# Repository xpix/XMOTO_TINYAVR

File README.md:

# Documentation for Motor Controller with PID Control to use a DC motor as stepper/servo

This code is designed for a motor controller and has merged the PID code of Josh Kopel with the code of the Makerbot servo-controller board. This code can be used on some boards by changing some values.

## Hardware Requirements

- motor controller as H-Bridge
- Hall Sensor PCB
- Ramps 1.4 stepper driver

## Software Requirements

- PID_v2.h library
- EEPROM.h library

## Code Explanation

### Motor Driver Type

The type of motor driver is defined using the `PWMCONTROL` variable. If `PWMCONTROL` is set to `1`, it means that the motor driver has only a PWM interface. In this case, the minimum and maximum values for PWM to turn the motor are defined using `PWMMIN` and `PWMMAX`.

### Pin Definitions

The pins used in the code are defined as follows:

- `encoder0PinA` and `encoder0PinB`: Pins for the Hall Sensor PCB
- `MotorIN1` and `MotorIN2`: Pins for the motor driver (if `PWMCONTROL` is set to `1`)
- `MotorDIR` and `MotorPWM`: Pins for the motor driver (if `PWMCONTROL` is set to `0`)
- `STEP_PIN` and `DIR_PIN`: Pins for the Ramps 1.4 stepper driver
- `EnableLED`: Pin for the LED that signals if the MCU is running

### PID Values

The default PID values are defined using the `MyObject` struct. The `kp`, `ki`, and `kd` values are set to `7.00`, `0.04`, and `0.20` respectively. These values can be changed by the user.

### Setup Function

In the `setup()` function, the following tasks are performed:

- Serial communication is started at a baud rate of 9600.
- The saved PID values are retrieved from the EEPROM. If no values are saved, the default values are used.
- The pins are set to their respective modes.
- Interrupts are attached to the `encoder0PinA` and `STEP_PIN` pins.
- The PID is set to automatic mode with a sample time of 2 and an output limit of -255 to 255.

### Loop Function

In the `loop()` function, the following tasks are performed:

- The set

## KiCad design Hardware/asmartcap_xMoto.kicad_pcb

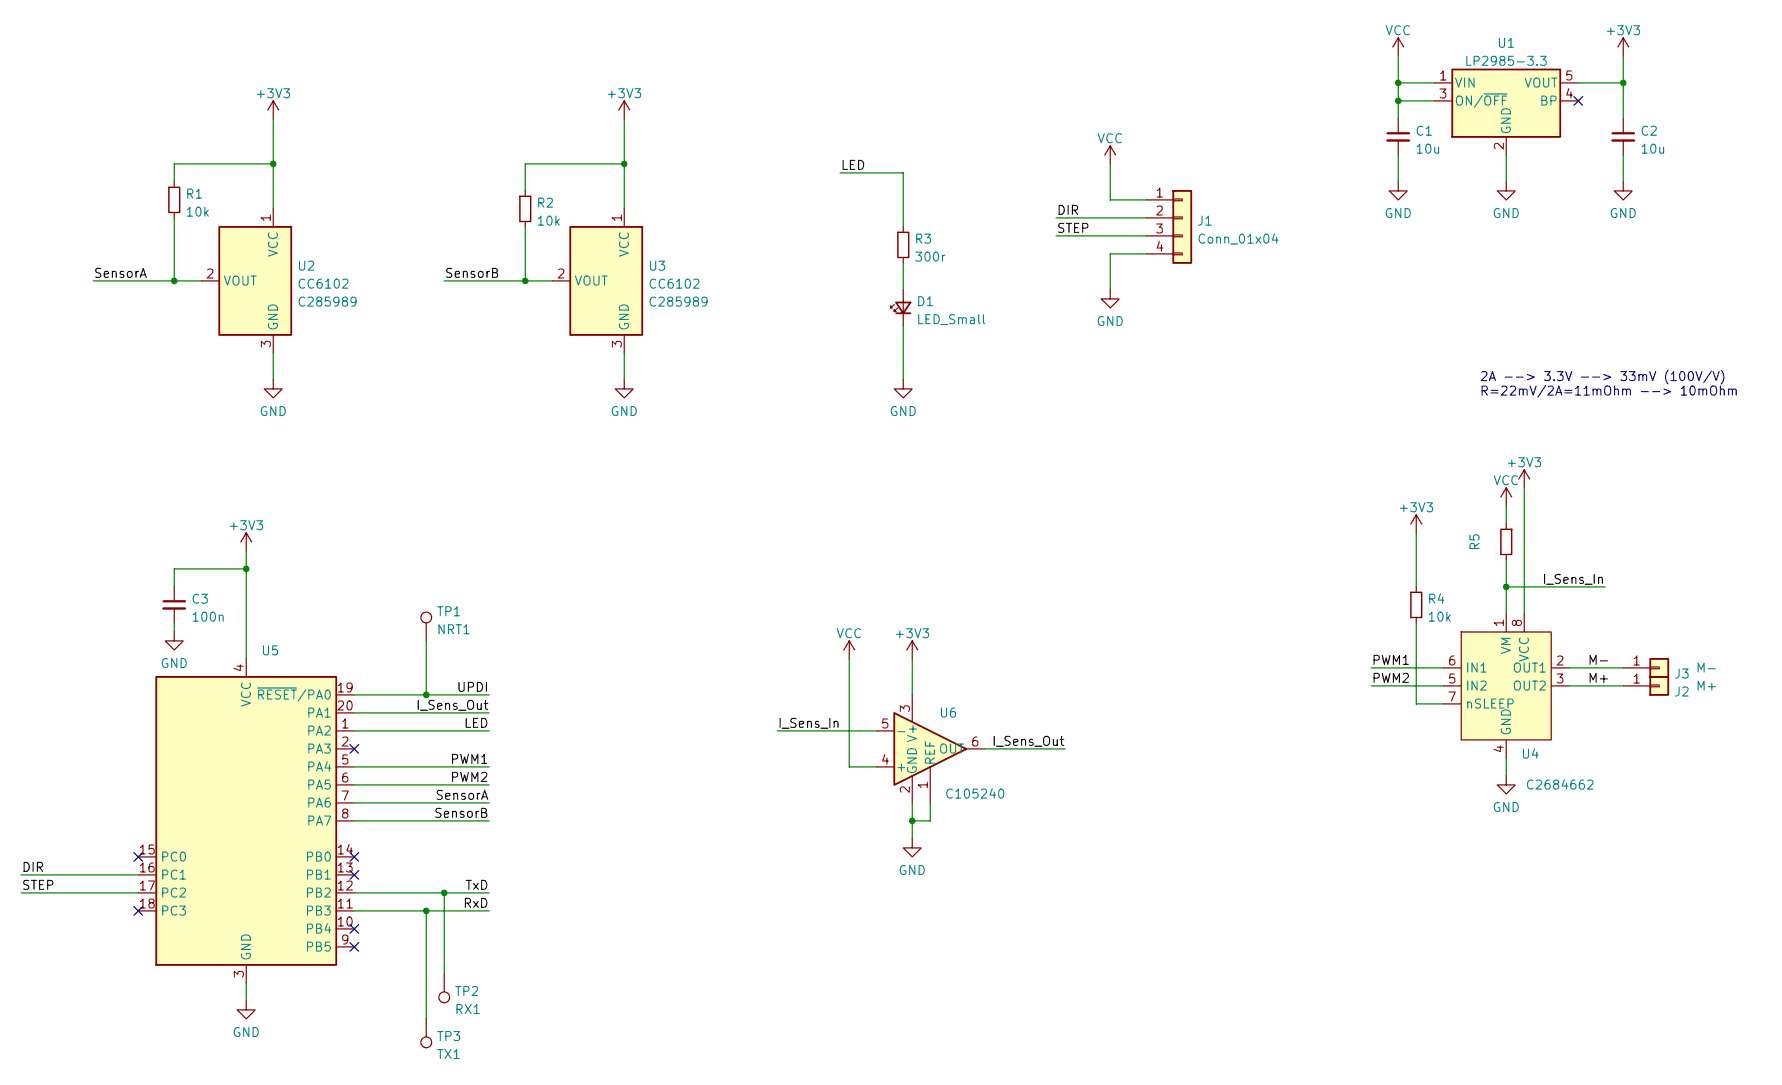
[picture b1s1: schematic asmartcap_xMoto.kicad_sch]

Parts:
C1, C2: 10u; C_0402_1005Metric; LCSC C15525
C3: 100n; C_0402_1005Metric
D1: LED_Small; LED_0402_1005Metric
J1: Conn_01x04; PinHeader_1x04_P2.54mm_Horizontal
J2: M+; TestPoint_Plated_Hole_D3.0mm
J3: M-; TestPoint_Plated_Hole_D3.0mm
R1, R2, R4: 10k; R_0402_1005Metric; MPN 0402WGF3000TCE; LCSC C25102
R3: 300r; R_0402_1005Metric
R5: MPN RTT03R010FTP; JLCPCB C158899
TP1: NRT1; TestPoint_Pad_D1.5mm
TP2: RX1; TestPoint_Pad_D1.5mm
TP3: TX1; TestPoint_Pad_D1.5mm
U1: LP2985-3.3; SOT-23-5
U2, U3: CC6102; TSOT-23; LCSC C285989
U4: LCSC C2684662
U5: (no value)
U6: JLCPCB C105240

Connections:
+3V3: C2.1, C3.1, R1.1, R2.1, R4.1, U1.5 (VOUT), U2.1 (VCC), U3.1 (VCC), U4.8 (VCC), U5.4 (VCC), U6.3 (V+)
/DIR: J1.2, U5.16 (PC1)
/I_Sens_In: R5.2, U4.1 (VM), U6.5 (-)
/I_Sens_Out: U5.20 (PA1), U6.6 (OUT)
/LED: R3.1, U5.1 (PA2)
/M+: J2.1, U4.3 (OUT2)
/M-: J3.1, U4.2 (OUT1)
/PWM1: U4.6 (IN1), U5.5 (PA4)
/PWM2: U4.5 (IN2), U5.6 (PA5)
/RxD: TP3.1, U5.11 (PB3)
/STEP: J1.3, U5.17 (PC2)
/SensorA: R1.2, U2.2 (VOUT), U5.7 (PA6)
/SensorB: R2.2, U3.2 (VOUT), U5.8 (PA7)
/TxD: TP2.1, U5.12 (PB2)
/UPDI: TP1.1, U5.19 (~RESET/PA0)
GND: C1.2, C2.2, C3.2, D1.1 (K), J1.4, U1.2 (GND), U2.3 (GND), U3.3 (GND), U4.4 (GND), U4.9 (Pad), U5.3 (GND), U5.21 (GND), U6.1 (REF), U6.2 (GND)
unnamed: D1.2 (A), R3.2
unnamed: R4.2, U4.7 (nSLEEP)
VCC: C1.1, J1.1, R5.1, U1.1 (VIN), U1.3 (ON/~OFF), U6.4 (+)

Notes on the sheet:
2A --> 3.3V --> 33mV (100V/V) R=22mV/2A=11mOhm --> 10mOhm

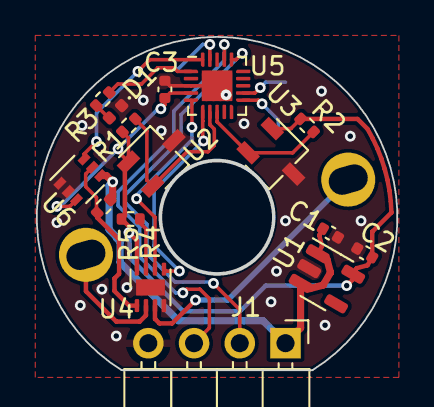
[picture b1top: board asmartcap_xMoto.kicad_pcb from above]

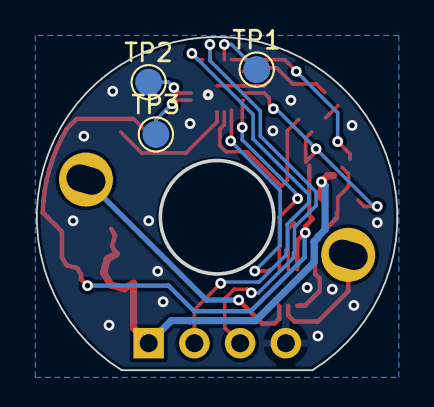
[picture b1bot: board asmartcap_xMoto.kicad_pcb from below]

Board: 2 copper layers, 19.9 x 18.4 mm, 21 parts (3 on the bottom side), 19 nets.

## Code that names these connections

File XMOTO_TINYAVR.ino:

/* 

i have made this code for the LMD18245 motor controller, 
i have merged the pid code of  Josh Kopel 
whith the code of makerbot servo-controller board,
you can use this code on the some board changing some values.
Daniele Poddighe

https://github.com/sebleedelisle/freeservo/tree/master/ServoStrap-master

Changes from Frank Herrmann for XMOTO and XMOTOD20

*/ 

#include <PID_v2.h>
#include <EEPROM.h>

#if defined(MILLIS_USE_TIMERA0)||defined(__AVR_ATtinyxy2__)
  #error "This sketch takes over TCA0, don't use for millis here.  Pin mappings on 8-pin parts are different"
#endif

// Type of Motordriver as is, with just an PWM Interface = true
// DRV8803
#define PWMCONTROL        1
#define PWMMIN           90 // minimum value for PWM to turn the motor
#define PWMMAX          200 // maximum value for PWM

#define EEPIDADDR         1 // Adress for saved PID Values

// Connect to Hall Sensor PCB
#define encoder0PinA  	2 // PA6
#define encoder0PinB  	3 // PA7

// If u need an revert, please change here the pins to motorcontroller
#if PWMCONTROL
  #define MotorIN1        1 // PA4
  #define MotorIN2        0 // PA5
#else
  #define MotorDIR    	  0 // PA4
  #define MotorPWM 		    1 // PA5
#endif

//from ramps 1.4 stepper driver
#define STEP_PIN	      12 // PC2
#define DIR_PIN         11 // PC1
#define EnableLED       15 // PB6


volatile long encoder0Pos = 0;

long GetSteps = 0;

// PID default values 
struct MyObject {
  double kp;
  double ki;
  double kd;
};
MyObject PIDvals = {
  1.35, 0.00, 0.01 // defaut values for PID
};

double input = 0, output = 0, setpoint = 0, error = 0;
PID myPID(&input, &output, &setpoint, PIDvals.kp, PIDvals.ki, PIDvals.kd, DIRECT);  

long LastInterval = 0;
long previousMillis = 0;        // will store last time LED was updated
bool dir     = false;

// ---------------------- SETUP -----------------------
void setup() { 
	Serial.begin(9600);

  pinMode(EnableLED, OUTPUT);
  digitalWrite (EnableLED, HIGH);

  // get Saved (EEPROM) or default PID Values
  MyObject PIDv;
  EEPROM.get(EEPIDADDR, PIDv);
  if(not (PIDv.kp > 0.01)){
     PIDv = {
        PIDvals.kp, PIDvals.ki, PIDvals.kd // defaut values
     };
  }
  myPID.SetTunings(PIDv.kp, PIDv.ki, PIDv.kd);
  Serial.println("Saved (EEPROM) or default PID Values:");
  Serial.println(PIDv.kp);
  Serial.println(PIDv.ki);
  Serial.println(PIDv.kd);

  myPID.SetMode(AUTOMATIC);     //set PID in Auto mode
  myPID.SetSampleTime(2);     // refresh rate of PID controller
  myPID.SetOutputLimits(-255, 255); // this is the MAX PWM value to move motor

	// Set Pins 
	pinMode(encoder0PinA, INPUT); 
	pinMode(encoder0PinB, INPUT);  

#if PWMCONTROL
  pinMode(MotorIN1, OUTPUT); 
  pinMode(MotorIN2, OUTPUT);
#else
	pinMode(MotorDIR, OUTPUT); 
	pinMode(MotorPWM, OUTPUT);
#endif


	//motor control Pins
	pinMode(STEP_PIN, INPUT_PULLUP);
	pinMode(DIR_PIN, INPUT);

	// Interupts for position and target steps 
	attachInterrupt(digitalPinToInterrupt(encoder0PinA), doEncoderMotor0, CHANGE);  // encoderA pin on interrupt
	attachInterrupt(digitalPinToInterrupt(STEP_PIN), 	   countStep, 	    RISING);  // interrupt to count steppules

	Serial.println("start");
	Serial.println("Position ToPosition MotorPWM RealPWM");

  delay(2000);
  digitalWrite (EnableLED, LOW);
} 

// ---------------------- LOOP -----------------------
void loop(){

  byte n = Serial.available();
  if (n != 0) {
    MyObject PIDv;
    PIDv.kp = Serial.parseFloat();
    PIDv.ki = Serial.parseFloat();
    PIDv.kd = Serial.parseFloat();

    // write only PID values in eeprom if not rubbish
    if( PIDv.kp > 0.00 && PIDv.ki > 0.00 && PIDv.kd > 0.00){
      MyObject PIDvals = {
        PIDv.kp, PIDv.ki, PIDv.kd // defaut values
      };
      Serial.println("Input PID values saved in eeprom:");
      EEPROM.put(EEPIDADDR, PIDvals);
  
      myPID.SetTunings(PIDv.kp, PIDv.ki, PIDv.kd);
    }

    // control PID values    
    Serial.println(PIDv.kp);
    Serial.println(PIDv.ki);
    Serial.println(PIDv.kd);
  }

	setpoint = GetSteps; // setpoint to Steps get from controller
	input = encoder0Pos; // real Position
  error = abs(setpoint - input);
  myPID.Compute();   // compute correct value
  int realpwm=0;
  if(error){
    realpwm = pwmOut(output);    // get PWM Value from PID calculated
  }
  else {
    realpwm = pwmOut(0);    // break
  }

  // Diganostic via serialplotter from arduino ide
  // Serial.println("Position ToPosition MotorPWM DIR");
  if(millis() - LastInterval > (abs(error) > 10 ? 100 : 1000)){

    if(output < PWMMIN){
      digitalWrite (EnableLED, HIGH); // signal that mcu is running
    }

    Serial.print(input);
    Serial.print(" ");
    Serial.print(setpoint);
    Serial.print(" ");
    Serial.print(output);
    Serial.print(" ");
    Serial.print(realpwm);
    Serial.println("");

    if(output < PWMMIN){
      digitalWrite (EnableLED, LOW);
    }
    LastInterval=millis();
  }
}

// ---------------------- SUBS -----------------------
#if PWMCONTROL
int pwmOut(int out) {
  int pwm = 0;
  if (out > 0) {
    // forward
    pwm = map(out, 0, 255, PWMMIN, PWMMAX );
    analogWrite ( MotorIN1, pwm );       
    digitalWrite ( MotorIN2, LOW );
  }
  else if (out < 0) {
    // reverse
    pwm = map(abs(out), 0, 255, PWMMIN, PWMMAX );
    digitalWrite ( MotorIN1, LOW );    // if REV < encoderValue motor move in reverse direction.   
    analogWrite ( MotorIN2, pwm );                      
  }
  else {
    // break
    digitalWrite ( MotorIN1, LOW );
    digitalWrite ( MotorIN2, LOW );
  }
  return pwm;
}
#else
void pwmOut(int out) {                               
	if (out > 0) {
		analogWrite( MotorPWM, out );      	
		digitalWrite ( MotorDIR ,LOW );
	}
	else {
		analogWrite( MotorPWM, abs(out) );                      
		digitalWrite ( MotorDIR, HIGH );		// if REV < encoderValue motor move in reverse direction.   
  }
}
#endif

void doEncoderMotor0(){
	if (digitalRead(encoder0PinA) == HIGH) {   // found a low-to-high on channel A
		if (digitalRead(encoder0PinB) == LOW) {  // check channel B to see which way
												 // encoder is turning
			encoder0Pos = encoder0Pos - 1;         // CCW
		} 
		else {
			encoder0Pos = encoder0Pos + 1;         // CW
		}
	}
	else                                        // found a high-to-low on channel A
	{ 
		if (digitalRead(encoder0PinB) == LOW) {   // check channel B to see which way
												  // encoder is turning  
			encoder0Pos = encoder0Pos + 1;          // CW
		} 
		else {
			encoder0Pos = encoder0Pos - 1;          // CCW
		}
	}
}

void countStep(){
	dir = digitalRead(DIR_PIN);
	if(dir == HIGH){
	  GetSteps++;
	}
	else{
	  GetSteps--;
	}
}

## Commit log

2022-07-25 initial version of XMOTO20D soft and ga
2023-07-22 fix PID write and get values from eeprom
2025-02-09 change some values and PID values
